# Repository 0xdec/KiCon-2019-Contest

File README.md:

# KiCon 2019 Contest!

This is a modified version of the KiCon 2019 conference badge.

## Rules

https://kicad-kicon.com/contest

## Original board files

https://github.com/orsonmmz/kicon19-badge-hw

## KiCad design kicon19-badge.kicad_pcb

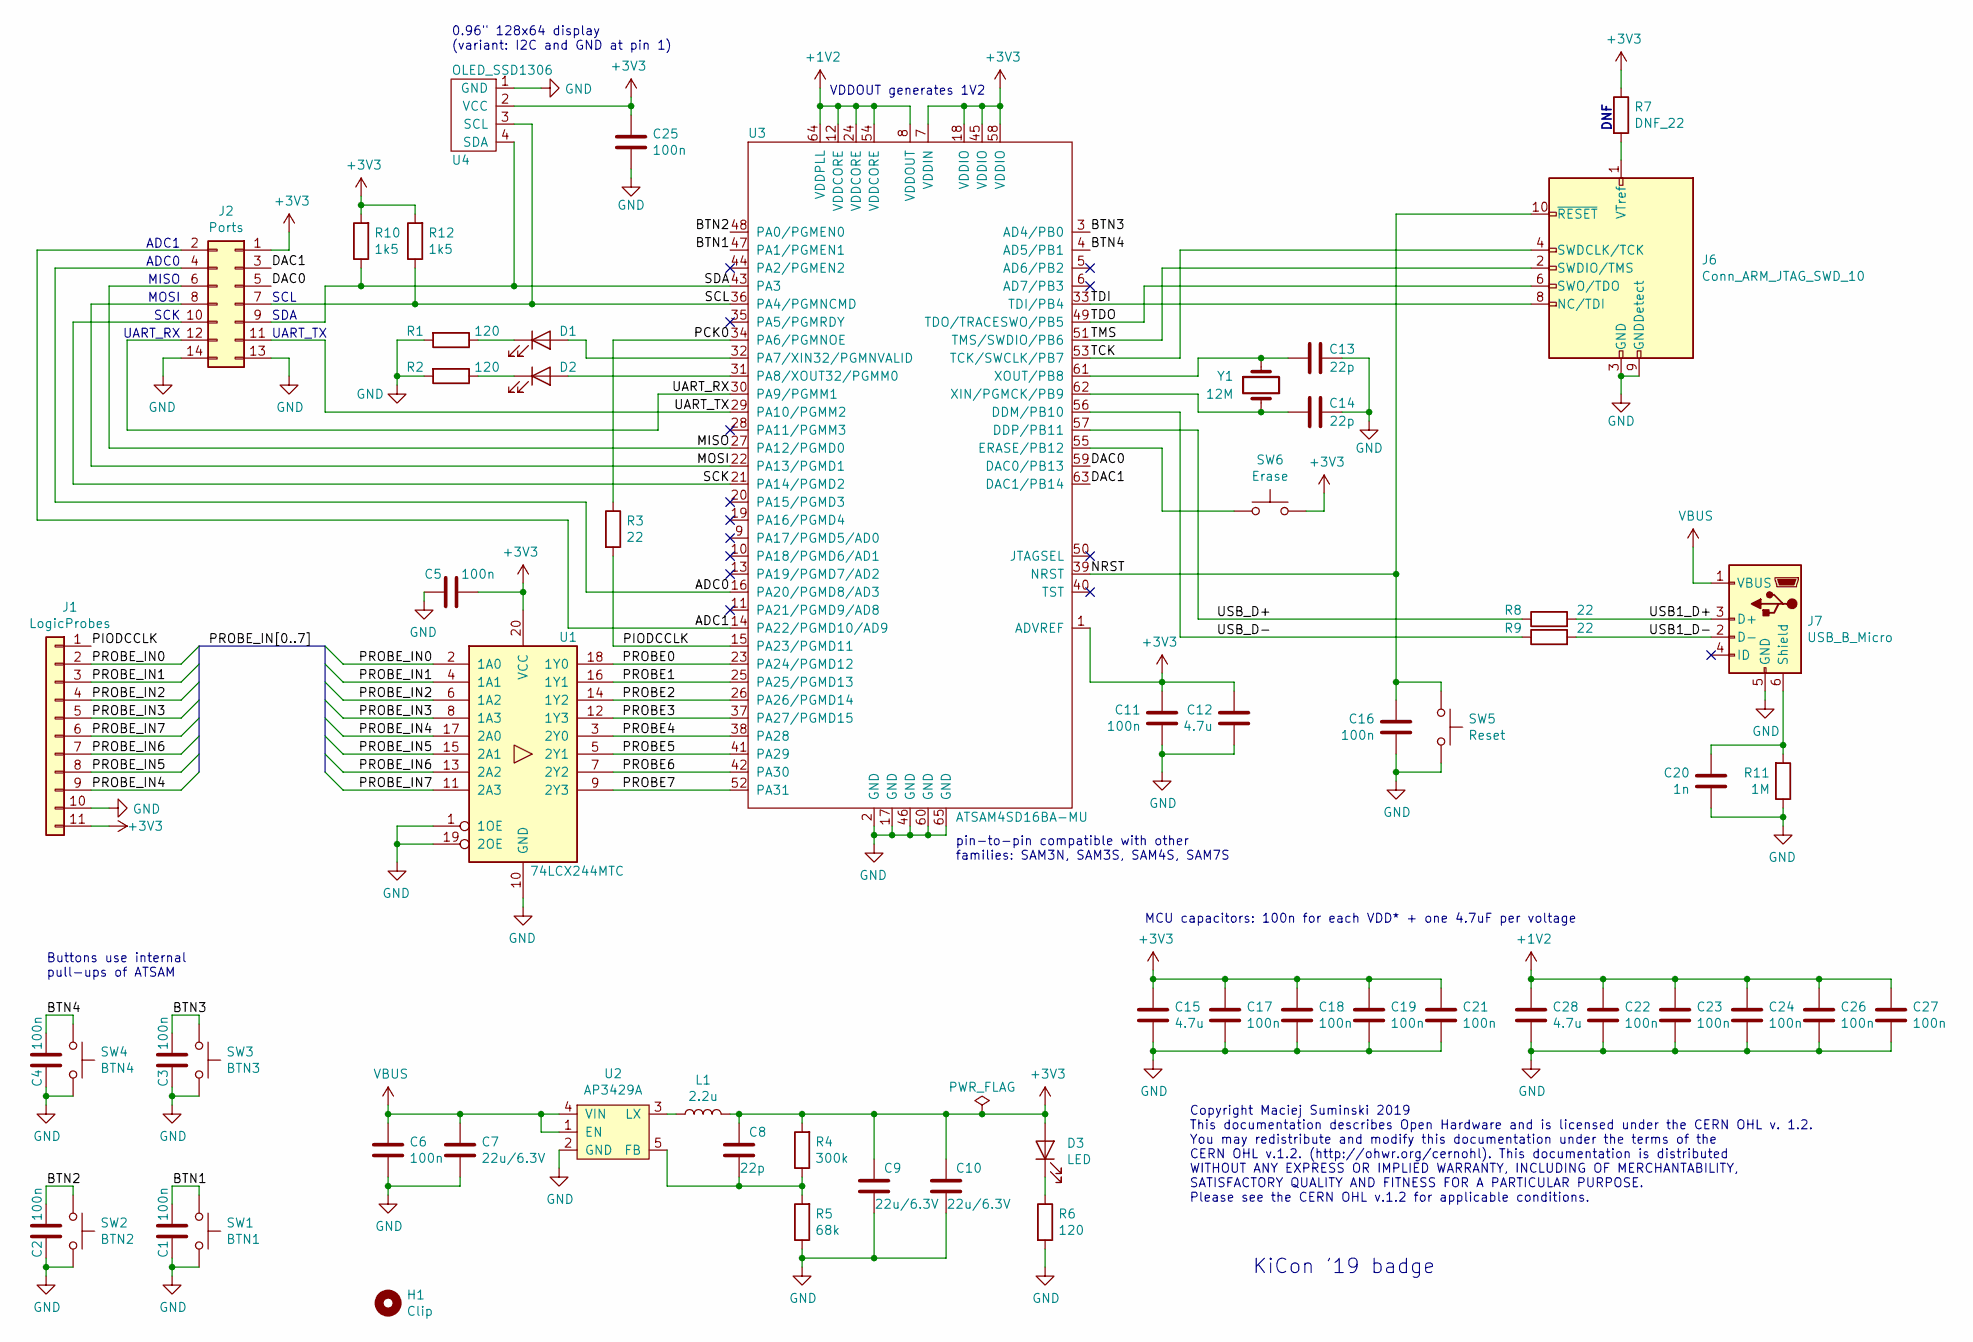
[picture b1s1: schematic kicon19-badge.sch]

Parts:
C1, C2, C3, C4, C5, C6, C11, C16, C17, C18, C19, C21, C22, C23, C24, C25, C26, C27: 100n; C_0603_1608Metric
C7, C9, C10: 22u/6.3V; C_0805_2012Metric
C8, C13, C14: 22p; C_0603_1608Metric
C12, C15, C28: 4.7u; C_0805_2012Metric
C20: 1n; C_0603_1608Metric
D1, D2, D3: LED; LED_0805_2012Metric
H1: Clip; ClipHole
J1: LogicProbes; PinHeader_1x11_P2.54mm_Horizontal
J2: Ports; PinHeader_2x07_P2.54mm_Horizontal
J6: Conn_ARM_JTAG_SWD_10; PinHeader_2x05_P1.27mm_Horizontal
J7: USB_B_Micro; 10118193-0001LF
L1: 2.2u; L_1007_2518Metric
R1, R2, R6: 120; R_0603_1608Metric
R3, R8, R9: 22; R_0603_1608Metric
R4: 300k; R_0603_1608Metric
R5: 68k; R_0603_1608Metric
R7: DNF_22; R_0603_1608Metric
R10, R12: 1k5; R_0603_1608Metric
R11: 1M; R_0603_1608Metric
SW1: BTN1; SW_SPST_PTS645
SW2: BTN2; SW_SPST_PTS645
SW3: BTN3; SW_SPST_PTS645
SW4: BTN4; SW_SPST_PTS645
SW5: Reset; SW_SPST_PTS645
SW6: Erase; SW_SPST_PTS645
U1: 74LCX244MTC; TSSOP-20_4.4x6.5mm_P0.65mm
U2: AP3429A; TSOT-23-5
U3: ATSAM4SD16BA-MU; QFN-64-1EP_9x9mm_P0.5mm_EP7.25x7.25mm
U4: OLED_SSD1306
Y1: 12M; Crystal_SMD_HC49-SD

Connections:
+1V2: C22.1, C23.1, C24.1, C26.1, C27.1, C28.1, U3.8 (VDDOUT), U3.12 (VDDCORE), U3.24 (VDDCORE), U3.54 (VDDCORE), U3.64 (VDDPLL)
+3V3: C5.2, C8.1, C9.1, C10.1, C11.1, C12.1, C15.1, C17.1, C18.1, C19.1, C21.1, C25.1, D3.2 (A), J1.11, J2.1, L1.2, R4.2, R7.1, R10.2, R12.2, SW6.1, U1.20 (VCC), U3.1 (ADVREF), U3.7 (VDDIN), U3.18 (VDDIO), U3.45 (VDDIO), U3.58 (VDDIO), U4.2 (VCC)
/ADC0: J2.4, U3.16 (PA20/PGMD8/AD3)
/ADC1: J2.2, U3.14 (PA22/PGMD10/AD9)
/BTN1: C1.2, SW1.2, U3.47 (PA1/PGMEN1)
/BTN2: C2.2, SW2.2, U3.48 (PA0/PGMEN0)
/BTN3: C3.2, SW3.2, U3.3 (AD4/PB0)
/BTN4: C4.2, SW4.2, U3.4 (AD5/PB1)
/DAC0: J2.5, U3.59 (DAC0/PB13)
/DAC1: J2.3, U3.63 (DAC1/PB14)
/MISO: J2.6, U3.27 (PA12/PGMD0)
/MOSI: J2.8, U3.22 (PA13/PGMD1)
/NRST: C16.2, J6.10 (~RESET~), SW5.2, U3.39 (NRST)
/PCK0: R3.1, U3.34 (PA6/PGMNOE)
/PIODCCLK: J1.1, R3.2, U3.15 (PA23/PGMD11)
/PROBE0: U1.18 (1Y0), U3.23 (PA24/PGMD12)
/PROBE1: U1.16 (1Y1), U3.25 (PA25/PGMD13)
/PROBE2: U1.14 (1Y2), U3.26 (PA26/PGMD14)
/PROBE3: U1.12 (1Y3), U3.37 (PA27/PGMD15)
/PROBE4: U1.3 (2Y0), U3.38 (PA28)
/PROBE5: U1.5 (2Y1), U3.41 (PA29)
/PROBE6: U1.7 (2Y2), U3.42 (PA30)
/PROBE7: U1.9 (2Y3), U3.52 (PA31)
/PROBE_IN0: J1.2, U1.2 (1A0)
/PROBE_IN1: J1.3, U1.4 (1A1)
/PROBE_IN2: J1.4, U1.6 (1A2)
/PROBE_IN3: J1.5, U1.8 (1A3)
/PROBE_IN4: J1.9, U1.17 (2A0)
/PROBE_IN5: J1.8, U1.15 (2A1)
/PROBE_IN6: J1.7, U1.13 (2A2)
/PROBE_IN7: J1.6, U1.11 (2A3)
/SCK: J2.10, U3.21 (PA14/PGMD2)
/SCL: J2.7, R12.1, U3.36 (PA4/PGMNCMD), U4.3 (SCL)
/SDA: J2.9, R10.1, U3.43 (PA3), U4.4 (SDA)
/TCK: J6.4 (SWDCLK/TCK), U3.53 (TCK/SWCLK/PB7)
/TDI: J6.8 (NC/TDI), U3.33 (TDI/PB4)
/TDO: J6.6 (SWO/TDO), U3.49 (TDO/TRACESWO/PB5)
/TMS: J6.2 (SWDIO/TMS), U3.51 (TMS/SWDIO/PB6)
/UART_RX: J2.12, U3.30 (PA9/PGMM1)
/UART_TX: J2.11, U3.29 (PA10/PGMM2)
/USB1_D+: J7.3 (D+), R8.2
/USB1_D-: J7.2 (D-), R9.2
/USB_D+: R8.1, U3.57 (DDP/PB11)
/USB_D-: R9.1, U3.56 (DDM/PB10)
GND: C1.1, C2.1, C3.1, C4.1, C5.1, C6.2, C7.2, C9.2, C10.2, C11.2, C12.2, C13.2, C14.2, C15.2, C16.1, C17.2, C18.2, C19.2, C20.2, C21.2, C22.2, C23.2, C24.2, C25.2, C26.2, C27.2, C28.2, J1.10, J2.13, J2.14, J6.3 (GND), J6.5 (GND), J6.9 (GNDDetect), J7.5 (GND), R1.2, R2.2, R5.1, R6.2, R11.1, SW1.1, SW2.1, SW3.1, SW4.1, SW5.1, U1.1 (1OE), U1.10 (GND), U1.19 (2OE), U2.2 (GND), U3.2 (GND), U3.17 (GND), U3.46 (GND), U3.60 (GND), U3.65 (GND), U4.1 (GND)
unnamed: C8.2, R4.1, R5.2, U2.5 (FB)
unnamed: C13.1, U3.61 (XOUT/PB8), Y1.1
unnamed: C14.1, U3.62 (XIN/PGMCK/PB9), Y1.2
unnamed: C20.1, J7.6 (Shield), R11.2
unnamed: D1.1 (K), R1.1
unnamed: D1.2 (A), U3.32 (PA7/XIN32/PGMNVALID)
unnamed: D2.1 (K), R2.1
unnamed: D2.2 (A), U3.31 (PA8/XOUT32/PGMM0)
unnamed: D3.1 (K), R6.1
unnamed: J6.1 (VTref), R7.2
unnamed: L1.1, U2.3 (LX)
unnamed: SW6.2, U3.55 (ERASE/PB12)
VBUS: C6.1, C7.1, J7.1 (VBUS), U2.1 (EN), U2.4 (VIN)

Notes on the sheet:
MCU capacitors: 100n for each VDD* + one 4.7uF per voltage
Buttons use internal pull-ups of ATSAM
0.96" 128x64 display (variant: I2C and GND at pin 1)
VDDOUT generates 1V2
pin-to-pin compatible with other families: SAM3N, SAM3S, SAM4S, SAM7S
ADC1
ADC0
MISO
MOSI
SCK
UART_RX
SCL
SDA
UART_TX
KiCon '19 badge
DNF
Copyright Maciej Suminski 2019 This documentation describes Open Hardware and is licensed under the CERN OHL v. 1.2. You may redistribute and modify this documentation under the terms of the CERN OHL v.1.2. (http://ohwr.org/cernohl). This documentation is distributed WITHOUT ANY EXPRESS OR IMPLIED 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

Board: 4 copper layers, 60 parts (1 on the bottom side), 58 nets, no tracks yet.

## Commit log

2019-04-27 Uploaded modified KiCon badge board files
    Modified from the files in this repository: https://github.com/orsonmmz/kicon19-badge-hw
2019-04-27 Updated README for the contest
2019-04-27 New directions for downloading
